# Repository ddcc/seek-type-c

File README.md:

# Writeup

https://www.dcddcc.com/blog/2018-11-10-retrofitting-the-seek-thermal-compact-with-a-usb-type-c-connector-using-3d-printing.html

# BOM

|RefDes|Vendor|Part Number|Specs|
|------|------|-----------|-----|
|J1|JAE|DX07P024AJ5R1500|Straddle Mount USB 3.1 Type-C Connector|
|R1/RD|Stackpole|RMCF0603JT5K10|5.1kΩ ± 10%, 0603 (0402) for board ≤ v2.0 (≥ v2.1), or equivalent|
|J3|Seek|PN307 SC 154|FPC Adapter (option 1)|
|J2|Amphenol|59453-051110EDHLF|5-position FFC Connector, 0.5mm pitch, Right-Angle (option 2)|
|N/A|N/A|N/A|FFC Ribbon, 0.5mm pitch (option 2)|

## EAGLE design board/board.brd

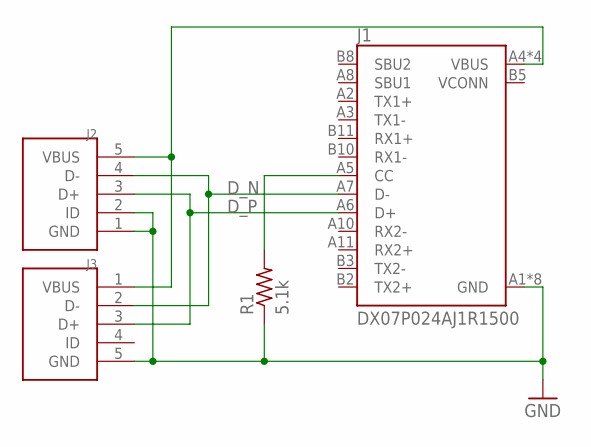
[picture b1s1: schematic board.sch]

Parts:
J1: DX07P024AJ1R1500; JAE_DX07P024AJ1R1500
J2: USB59453-051110EDHLF; 59453-051110EDHLF
J3: USBSEEK-USB; SEEK-USB
R1: 5.1k; R0402

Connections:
D_N: J1.A7 (D-), J2.4 (D-), J3.2 (D-)
D_P: J1.A6 (D+), J2.3 (D+), J3.3 (D+)
GND: J1.A1 (GND), J1.A12 (GND), J1.B0 (GND), J1.B1 (GND), J1.B12 (GND), J1.B13 (GND), J1.B17 (GND), J1.B18 (GND), J2.1 (GND), J2.2 (ID), J3.5 (GND), R1.1
unnamed: J1.A5 (CC), R1.2
VBUS: J1.A4 (VBUS), J1.A9 (VBUS), J1.B4 (VBUS), J1.B9 (VBUS), J2.5 (VBUS), J3.1 (VBUS)
VCONN: J1.B5 (VCONN)

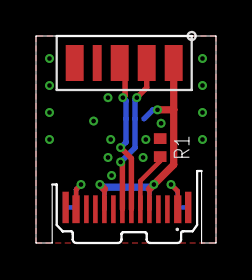
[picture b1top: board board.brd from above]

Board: 2 copper layers, 10.0 x 11.5 mm, 4 parts (1 on the bottom side), 5 nets.

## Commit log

2019-12-16 initial import
2020-06-20 add more files
